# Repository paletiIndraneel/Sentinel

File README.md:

# Sentinel v1.0 firmware

Sentinel continuously monitors three-phase AC voltage and true internet
availability. It is an ESP32-S3 PlatformIO/Arduino project designed for the
provided controller PCB: ADS1115, DS3231, 128x64 SSD1306 OLED, microSD, and an
optional SHT31.

## Features

- 1-second RMS windows for R, Y, and B phase measurements
- Phase loss, under-voltage, over-voltage, and phase-imbalance events
- Internet reachability test using asynchronous TCP to a public endpoint
- Automatic Wi-Fi recovery without blocking `loop()`
- DS3231 ISO-8601 timestamps
- `events.csv` and `readings.csv` on a FAT32 microSD card
- OLED current voltage, connectivity, and fault status

## Project layout

```text
include/    Public module interfaces and configuration
src/        Module implementations and application composition root
lib/        Reserved for local libraries
docs/       Reserved for commissioning and operating documentation
hardware/   Reserved for released hardware assets
```

## Configure and flash

1. Install PlatformIO and open this directory.
2. Set `WIFI_SSID` and `WIFI_PASSWORD` in [include/config.h](include/config.h).
3. Verify `PHASE_SCALE`, phase-loss, under/over-voltage and imbalance limits
   against the installation requirements. Each ZMPT101B channel must be
   calibrated with an isolated, trusted reference meter.
4. Insert a FAT32 microSD card and upload:

   ```powershell
   pio run --target upload
   pio device monitor --baud 115200
   ```

## Connectivity behavior

The device distinguishes internet availability from mere association with a
Wi-Fi access point. It makes a non-blocking HTTP request to `1.1.1.1` every
minute. A 2xx response marks the internet `ONLINE`; connection failure or a
timeout marks it `OFFLINE`. Wi-Fi retry timing and endpoint configuration are
in `config.h`. No router monitoring, cloud connection, MQTT, OTA, dashboard,
or mobile functionality is included.

## Pin map

| Function | ESP32-S3 GPIO |
| --- | ---: |
| Status LED / Wi-Fi LED | 4 / 5 |
| I2C SDA / SCL | 8 / 9 |
| microSD CS / MOSI / SCK / MISO | 10 / 11 / 12 / 13 |

## Safety

This product interfaces with mains voltage. Commission only with suitable
isolation, enclosure, fusing and a qualified person. Default calibration is
`1.0` and is not a valid mains-voltage reading.

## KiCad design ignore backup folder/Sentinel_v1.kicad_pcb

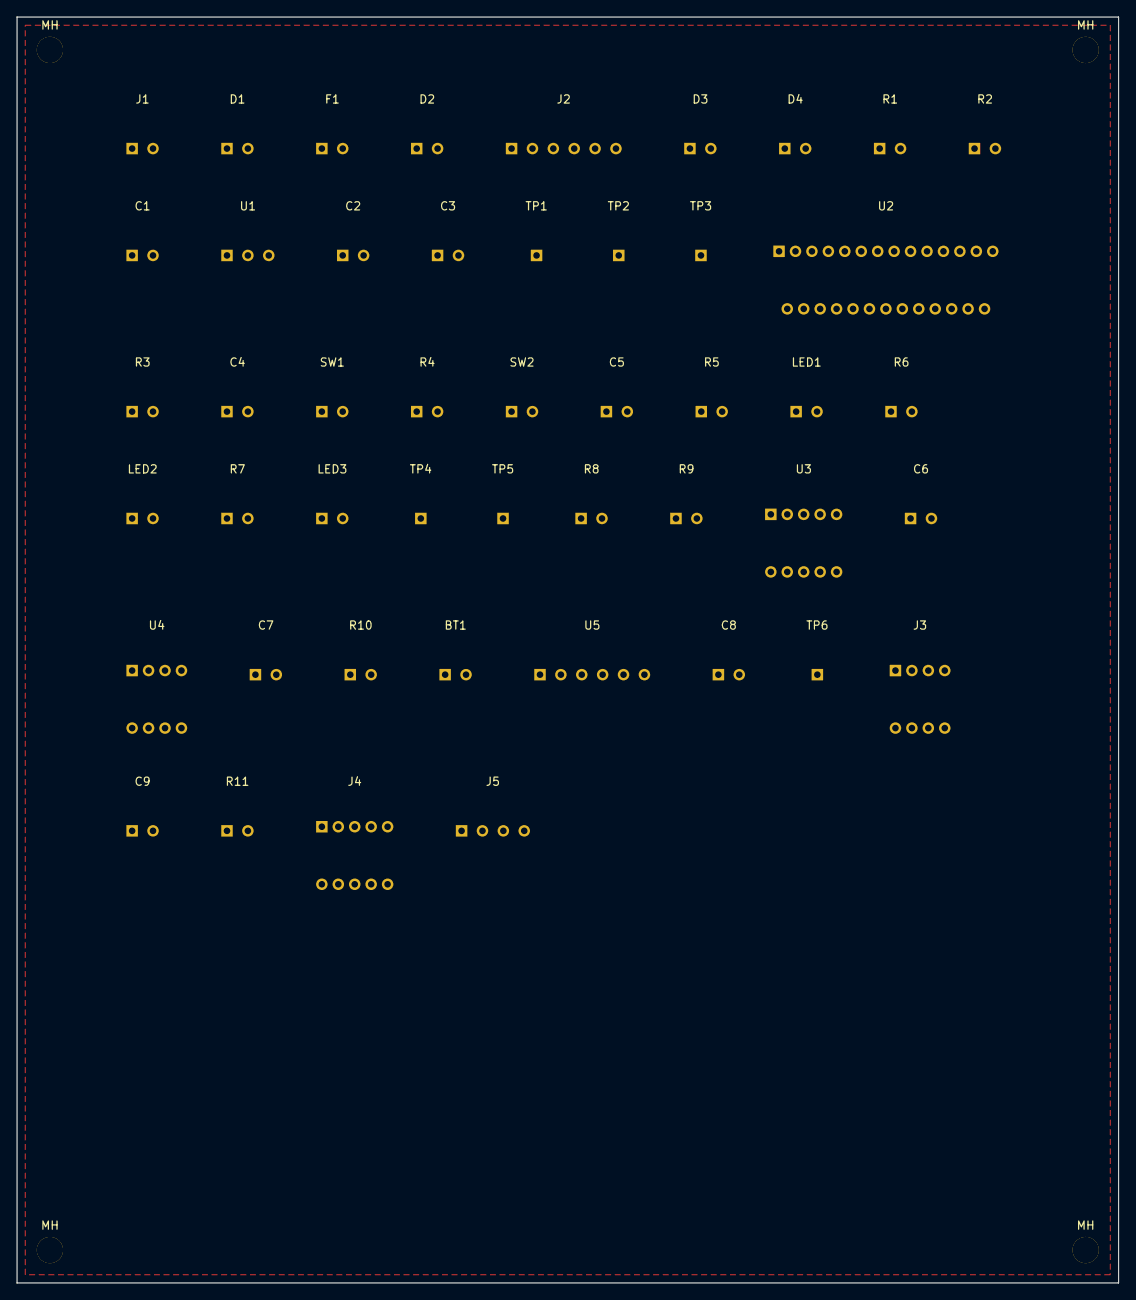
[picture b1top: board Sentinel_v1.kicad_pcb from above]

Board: 2 copper layers, 134.0 x 154.0 mm, 51 parts (0 on the bottom side), 38 nets, no tracks yet.

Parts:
BT1: CR2032; BatteryHolder_Keystone_3034_1x20mm
C1, C2: 10uF; C_0603_1608Metric
C3, C4: 1uF; C_0603_1608Metric
C5, C6, C7, C8, C9: 0.1uF; C_0603_1608Metric
D1, D2, D3: SS34; D_SOD-123
D4: SMBJ5.0A; D_SOD-123
F1: MF-R500; Fuse_1210_3225Metric
J1: 5V_UPS_IN; TerminalBlock_bornier-2_P5.08mm
J2: USB-C; USB_C_Receptacle_HRO_TYPE-C-31-M-12
J3: MicroSD; microSD_HC_Molex-104031-0811
J4: EXP_HDR; PinHeader_2x05_P2.54mm_Vertical
J5: J_SENSOR; JST_XH_B4B-XH-A_1x04_P2.50mm_Vertical
LED1: STATUS; LED_0603_1608Metric
LED2: WIFI; LED_0603_1608Metric
LED3: PWR; LED_0603_1608Metric
MH: M3; MountingHole_3.2mm_M3
MH#2, MH#3, MH#4: M3; MountingHole_3.2mm_M3
R1, R2: 5.1k; R_0603_1608Metric
R3, R4, R10, R11: 10k; R_0603_1608Metric
R5, R6, R7: 330R; R_0603_1608Metric
R8, R9: 4.7k; R_0603_1608Metric
SW1: SW_RESET; SW_SPST_TL3342
SW2: SW_BOOT; SW_SPST_TL3342
TP1: TP_5V; TestPoint_Pad_1.5x1.5mm
TP2: TP_3V3; TestPoint_Pad_1.5x1.5mm
TP3: TP_GND; TestPoint_Pad_1.5x1.5mm
TP4: TP_SDA; TestPoint_Pad_1.5x1.5mm
TP5: TP_SCL; TestPoint_Pad_1.5x1.5mm
TP6: TP_A3_RSV; TestPoint_Pad_1.5x1.5mm
U1: AMS1117-3.3; SOT-223-3_TabPin2
U2: ESP32-S3-WROOM-1; ESP32-S2-MINI-1
U3: ADS1115; MSOP-10_3x3mm_P0.5mm
U4: DS3231; SOIC-16W_7.5x10.3mm_P1.27mm
U5: SHT31; DFN-8-1EP_2.5x2.5mm_P0.5mm_EP1.2x1.6mm

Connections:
3V3: C2.1, C3.1, C5.1, C6.1, C7.1, C8.1, C9.1, J3.3, J4.1, R3.1, R4.1, R7.1, R8.1, R9.1, R10.1, R11.1, TP2.1, U1.3, U2.1, U3.1, U4.1, U5.1
5V_A: D2.1, F1.2
5V_UPS_IN: D1.1, J1.1
5V_UPS_PROT: D1.2, F1.1
ADC_A3_RSV: TP6.1, U3.10
ADS_ALRT: U2.7, U3.6
BOOT: R4.2, SW2.1, U2.4
EN: C4.1, R3.2, SW1.1, U2.3
EXP_IO15: J4.3, U2.18
EXP_IO16: J4.4, U2.19
EXP_IO17: J4.5, U2.20
EXP_IO18: J4.6, U2.21
EXP_IO21: J4.7, U2.22
EXP_IO47: J4.8, U2.23
EXP_IO48: J4.9, U2.24
GND: BT1.2, C1.2, C2.2, C3.2, C4.2, C5.2, C6.2, C7.2, C8.2, C9.2, D4.2, J1.2, J2.2, J3.5, J3.8, J4.2, J4.10, J5.4, LED1.2, LED2.2, LED3.2, R1.2, R2.2, SW1.2, SW2.2, TP3.1, U1.2, U2.2, U2.25, U2.26, U2.27, U3.2, U3.5, U4.2, U5.2, U5.5
PHASE_B_ADC: J5.3, U3.9
PHASE_R_ADC: J5.1, U3.7
PHASE_Y_ADC: J5.2, U3.8
PWR_LED_A: LED3.1, R7.2
RTC_RST: R10.2, U4.7
SCL: R9.2, TP5.1, U2.9, U3.3, U4.4, U5.4
SDA: R8.2, TP4.1, U2.8, U3.4, U4.3, U5.3
SD_CS: J3.1, R11.2, U2.10
SD_MISO: J3.6, U2.13
SD_MOSI: J3.2, U2.11
SD_SCK: J3.4, U2.12
STATUS_GPIO: R5.1, U2.5
STATUS_LED_A: LED1.1, R5.2
USB_CC1: J2.5, R1.1
USB_CC2: J2.6, R2.1
USB_DM: J2.4, U2.14
USB_DP: J2.3, U2.15
VBAT: BT1.1, U4.8
VBUS_USB: D3.1, J2.1
VCC_5V: C1.1, D2.2, D3.2, D4.1, TP1.1, U1.1
WIFI_GPIO: R6.1, U2.6
WIFI_LED_A: LED2.1, R6.2

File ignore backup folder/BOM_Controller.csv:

Reference,Value,Footprint,Sheet
BT1,CR2032 Battery,Battery:BatteryHolder_Keystone_3034_1x20mm,Sensors_I2C
C1,10uF Bulk 5V,Capacitor_SMD:C_0603_1608Metric,Power
C2,10uF Bulk 3V3,Capacitor_SMD:C_0603_1608Metric,Power
C3,1uF 3V3,Capacitor_SMD:C_0603_1608Metric,Power
C4,1uF EN Delay,Capacitor_SMD:C_0603_1608Metric,MCU_Core
C5,0.1uF ESP32 Decouple,Capacitor_SMD:C_0603_1608Metric,MCU_Core
C6,0.1uF ADS1115 Decouple,Capacitor_SMD:C_0603_1608Metric,Sensors_I2C
C7,0.1uF DS3231 Decouple,Capacitor_SMD:C_0603_1608Metric,Sensors_I2C
C8,0.1uF SHT31 Decouple,Capacitor_SMD:C_0603_1608Metric,Sensors_I2C
C9,0.1uF SD Decouple,Capacitor_SMD:C_0603_1608Metric,Storage
D1,SS34 (Reverse Polarity),Diode_SMD:D_SOD-123,Power
D2,SS34 (OR-ing UPS),Diode_SMD:D_SOD-123,Power
D3,SS34 (OR-ing USB),Diode_SMD:D_SOD-123,Power
D4,SMBJ5.0A,Diode_SMD:D_SOD-123,Power
F1,MF-R500 500mA,Fuse:Fuse_1210_3225Metric,Power
J1,5V_UPS_IN,TerminalBlock:TerminalBlock_bornier-2_P5.08mm,Power
J2,USB-C Prog Port,Connector_USB:USB_C_Receptacle_HRO_TYPE-C-31-M-12,Power
J3,MicroSD Socket,Connector_Card:microSD_HC_Molex-104031-0811,Storage
J4,EXPANSION HDR,Connector_PinHeader_2.54mm:PinHeader_2x05_P2.54mm_Vertical,Expansion
J5,J_TO_SENSOR_BOARD,Connector_JST:JST_XH_B4B-XH-A_1x04_P2.50mm_Vertical,Connector
LED1,STATUS (Green),LED_SMD:LED_0603_1608Metric,MCU_Core
LED2,WIFI (Blue),LED_SMD:LED_0603_1608Metric,MCU_Core
LED3,PWR (Red),LED_SMD:LED_0603_1608Metric,MCU_Core
R1,5.1k CC1,Resistor_SMD:R_0603_1608Metric,Power
R10,10k RTC RST Pullup,Resistor_SMD:R_0603_1608Metric,Sensors_I2C
R11,10k SD_CS Pullup,Resistor_SMD:R_0603_1608Metric,Storage
R2,5.1k CC2,Resistor_SMD:R_0603_1608Metric,Power
R3,10k EN Pullup,Resistor_SMD:R_0603_1608Metric,MCU_Core
R4,10k BOOT Pullup,Resistor_SMD:R_0603_1608Metric,MCU_Core
R5,330R Status LED,Resistor_SMD:R_0603_1608Metric,MCU_Core
R6,330R WiFi LED,Resistor_SMD:R_0603_1608Metric,MCU_Core
R7,330R Power LED,Resistor_SMD:R_0603_1608Metric,MCU_Core
R8,4.7k SDA Pullup,Resistor_SMD:R_0603_1608Metric,Sensors_I2C
R9,4.7k SCL Pullup,Resistor_SMD:R_0603_1608Metric,Sensors_I2C
SW1,SW_RESET,Button_Switch_SMD:SW_SPST_TL3342,MCU_Core
SW2,SW_BOOT,Button_Switch_SMD:SW_SPST_TL3342,MCU_Core
TP1,TP_5V,TestPoint:TestPoint_Pad_1.5x1.5mm,Power
TP2,TP_3V3,TestPoint:TestPoint_Pad_1.5x1.5mm,Power
TP3,TP_GND,TestPoint:TestPoint_Pad_1.5x1.5mm,Power
TP4,TP_SDA,TestPoint:TestPoint_Pad_1.5x1.5mm,MCU_Core
TP5,TP_SCL,TestPoint:TestPoint_Pad_1.5x1.5mm,MCU_Core
TP6,TP_A3_RSV,TestPoint:TestPoint_Pad_1.5x1.5mm,Sensors_I2C
U1,AMS1117-3.3,Package_TO_SOT_SMD:SOT-223-3_TabPin2,Power
U2,ESP32-S3-WROOM-1,RF_Module:ESP32-S2-MINI-1,MCU_Core
U3,ADS1115 16-bit ADC,Package_SO:MSOP-10_3x3mm_P0.5mm,Sensors_I2C
U4,DS3231 RTC,Package_SO:SOIC-16W_7.5x10.3mm_P1.27mm,Sensors_I2C
U5,SHT31 Temp/Humidity,Package_DFN_QFN:DFN-8-1EP_2.5x2.5mm_P0.5mm_EP1.2x1.6mm,Sensors_I2C

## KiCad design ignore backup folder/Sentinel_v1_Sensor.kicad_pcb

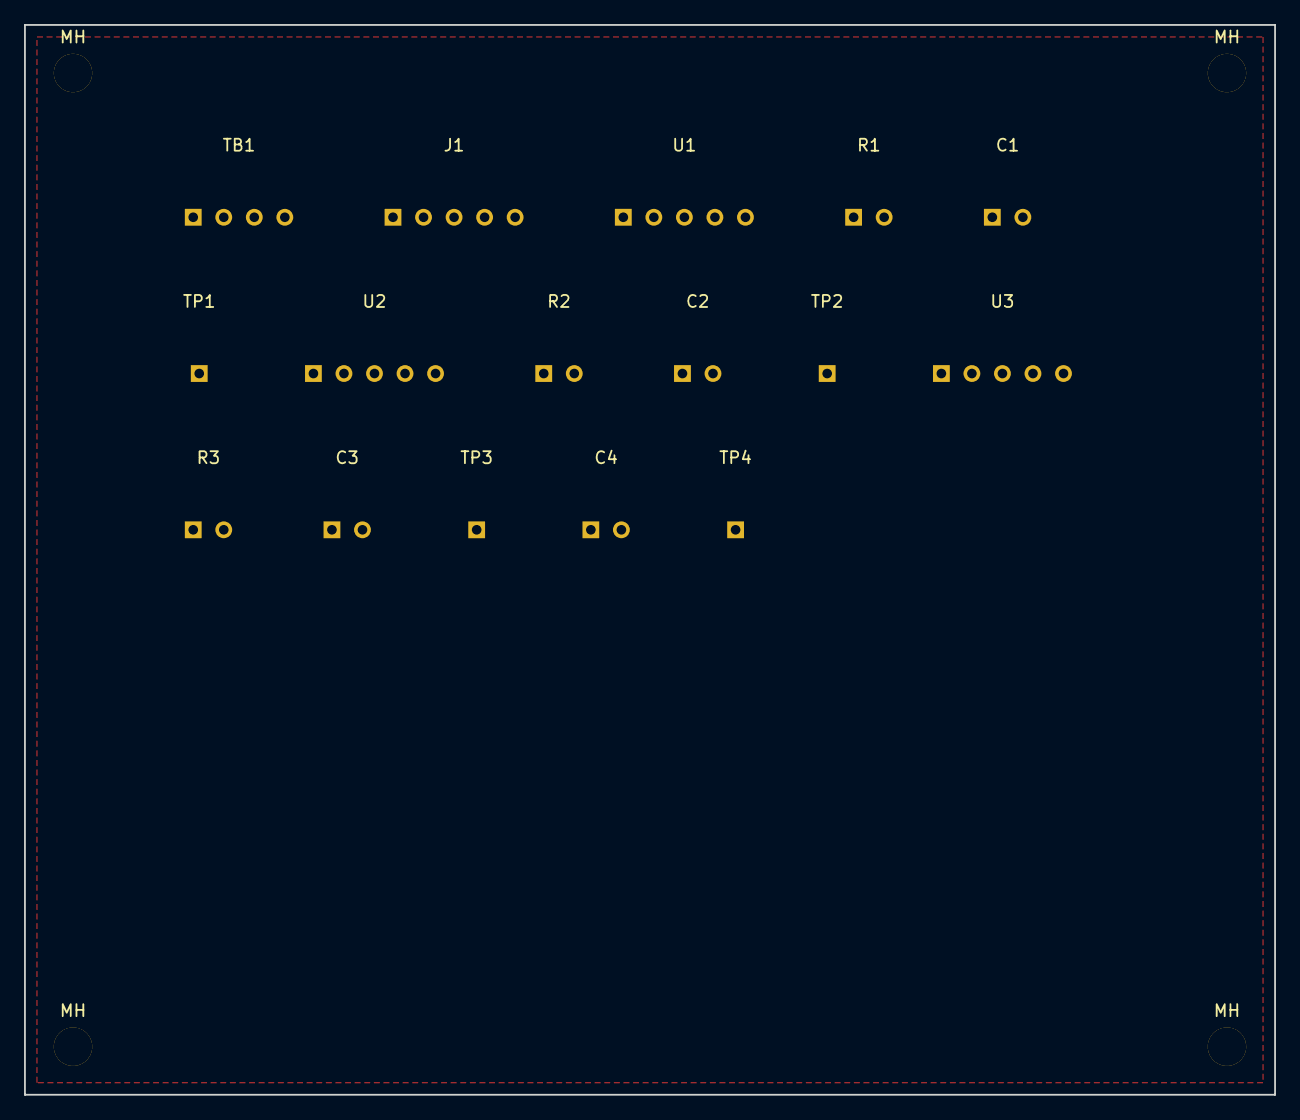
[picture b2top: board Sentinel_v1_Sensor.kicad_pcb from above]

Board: 2 copper layers, 104.0 x 89.0 mm, 20 parts (0 on the bottom side), 12 nets, no tracks yet.

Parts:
C1, C2, C3: 100nF; C_0603_1608Metric
C4: 10uF; C_0603_1608Metric
J1: J_CTRL; JST_XH_B5B-XH-A_1x05_P2.50mm_Vertical
MH: M3; MountingHole_3.2mm_M3
MH#2, MH#3, MH#4: M3; MountingHole_3.2mm_M3
R1, R2, R3: 1k; R_0603_1608Metric
TB1: MAINS; TerminalBlock_bornier-4_P5.08mm
TP1: TP_R; TestPoint_Pad_1.5x1.5mm
TP2: TP_Y; TestPoint_Pad_1.5x1.5mm
TP3: TP_B; TestPoint_Pad_1.5x1.5mm
TP4: TP_GND; TestPoint_Pad_1.5x1.5mm
U1: ZMPT-R; ZMPT101B_Module
U2: ZMPT-Y; ZMPT101B_Module
U3: ZMPT-B; ZMPT101B_Module

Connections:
MAINS_B: TB1.3, U3.1
MAINS_N: TB1.4, U1.2, U2.2, U3.2
MAINS_R: TB1.1, U1.1
MAINS_Y: TB1.2, U2.1
OUT_B: C3.1, J1.5, R3.2, TP3.1
OUT_R: C1.1, J1.3, R1.2, TP1.1
OUT_Y: C2.1, J1.4, R2.2, TP2.1
SNS_5V: C4.1, J1.1, U1.3, U2.3, U3.3
SNS_GND: C1.2, C2.2, C3.2, C4.2, J1.2, TP4.1, U1.4, U2.4, U3.4
ZMPT_B_RAW: R3.1, U3.5
ZMPT_R_RAW: R1.1, U1.5
ZMPT_Y_RAW: R2.1, U2.5

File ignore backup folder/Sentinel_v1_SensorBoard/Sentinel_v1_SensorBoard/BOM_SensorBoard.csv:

Reference,Value,Footprint,Sheet
C1,100nF LPF,Capacitor_SMD:C_0603_1608Metric,AC_Sensor_Board
C2,100nF LPF,Capacitor_SMD:C_0603_1608Metric,AC_Sensor_Board
C3,100nF LPF,Capacitor_SMD:C_0603_1608Metric,AC_Sensor_Board
C4,10uF SNS_5V Decouple,Capacitor_SMD:C_0603_1608Metric,AC_Sensor_Board
J1,J_TO_CONTROLLER,Connector_JST:JST_XH_B5B-XH-A_1x05_P2.50mm_Vertical,AC_Sensor_Board
R1,1k Protection R,Resistor_SMD:R_0603_1608Metric,AC_Sensor_Board
R2,1k Protection R,Resistor_SMD:R_0603_1608Metric,AC_Sensor_Board
R3,1k Protection R,Resistor_SMD:R_0603_1608Metric,AC_Sensor_Board
TB1,MAINS R/Y/B/N,TerminalBlock:TerminalBlock_bornier-4_P5.08mm,AC_Sensor_Board
TP1,TP_OUT_R,TestPoint:TestPoint_Pad_1.5x1.5mm,AC_Sensor_Board
TP2,TP_OUT_Y,TestPoint:TestPoint_Pad_1.5x1.5mm,AC_Sensor_Board
TP3,TP_OUT_B,TestPoint:TestPoint_Pad_1.5x1.5mm,AC_Sensor_Board
TP4,TP_SNS_GND,TestPoint:TestPoint_Pad_1.5x1.5mm,AC_Sensor_Board
U1,ZMPT101B Phase-R,Sentinel:ZMPT101B_Module,AC_Sensor_Board
U2,ZMPT101B Phase-Y,Sentinel:ZMPT101B_Module,AC_Sensor_Board
U3,ZMPT101B Phase-B,Sentinel:ZMPT101B_Module,AC_Sensor_Board

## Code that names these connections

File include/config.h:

#pragma once

#include <Arduino.h>

namespace sentinel::config {
// Keep credentials out of source control in a private config override.
#if __has_include("config_private.h")
#include "config_private.h"
#else
constexpr char WIFI_SSID[] = "CHANGE_ME";
constexpr char WIFI_PASSWORD[] = "CHANGE_ME";
#endif

// Public HTTP endpoint used only to verify internet reachability. It bypasses
// DNS deliberately, so a successful result proves routing beyond the LAN.
  
constexpr char INTERNET_TEST_HOST[] = "www.google.com";
constexpr uint16_t INTERNET_TEST_PORT = 80;

namespace pin {
constexpr uint8_t STATUS_LED = 4;
constexpr uint8_t WIFI_LED = 5;
constexpr uint8_t TRAFFIC_RED = 25;
constexpr uint8_t TRAFFIC_YELLOW = 26;
constexpr uint8_t TRAFFIC_GREEN = 27;
constexpr uint8_t I2C_SDA = 21;
constexpr uint8_t I2C_SCL = 22;
constexpr uint8_t SD_CS = 10;
constexpr uint8_t SD_MOSI = 11;
constexpr uint8_t SD_SCK = 12;
constexpr uint8_t SD_MISO = 13;
}  // namespace pin

constexpr uint32_t VOLTAGE_SAMPLE_INTERVAL_MS = 4;
constexpr uint32_t VOLTAGE_WINDOW_MS = 1000;
constexpr uint32_t READING_LOG_INTERVAL_MS = 60000;
constexpr uint32_t DISPLAY_INTERVAL_MS = 500;
constexpr uint32_t ENVIRONMENT_INTERVAL_MS = 5000;
constexpr uint32_t WIFI_CONNECT_TIMEOUT_MS = 15000;
constexpr uint32_t WIFI_RETRY_INTERVAL_MS = 30000;
constexpr uint32_t INTERNET_TEST_INTERVAL_MS = 60000;
constexpr uint32_t INTERNET_TEST_TIMEOUT_MS = 7000;

// Calibrate each channel with an isolated, trusted reference meter before use.
constexpr float PHASE_SCALE[] = {1.0F, 1.0F, 1.0F};
constexpr float PHASE_LOSS_V = 80.0F;
constexpr float UNDER_VOLTAGE_V = 180.0F;
constexpr float OVER_VOLTAGE_V = 260.0F;
constexpr float MAX_IMBALANCE_PERCENT = 5.0F;
}  // namespace sentinel::config
